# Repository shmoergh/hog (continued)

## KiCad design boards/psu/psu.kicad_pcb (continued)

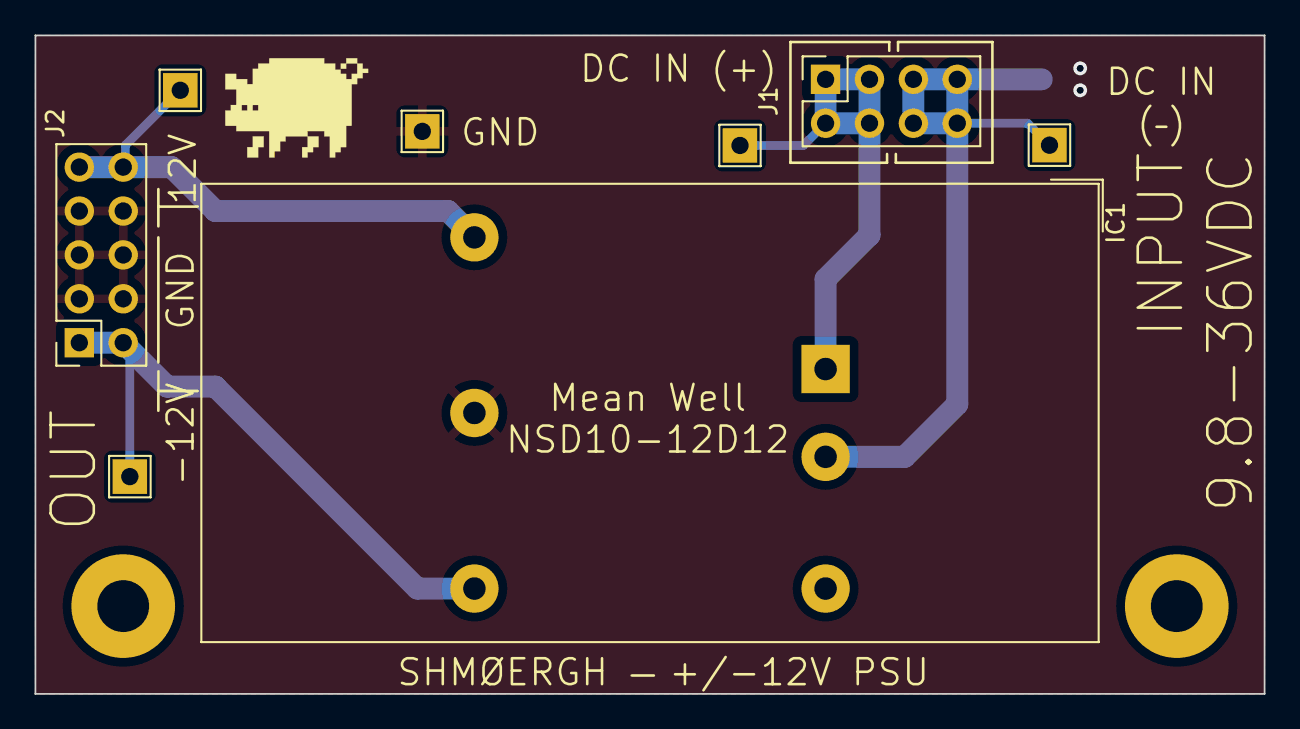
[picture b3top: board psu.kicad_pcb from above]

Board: 2 copper layers, 71.1 x 38.1 mm, 11 parts (1 on the bottom side), 5 nets.

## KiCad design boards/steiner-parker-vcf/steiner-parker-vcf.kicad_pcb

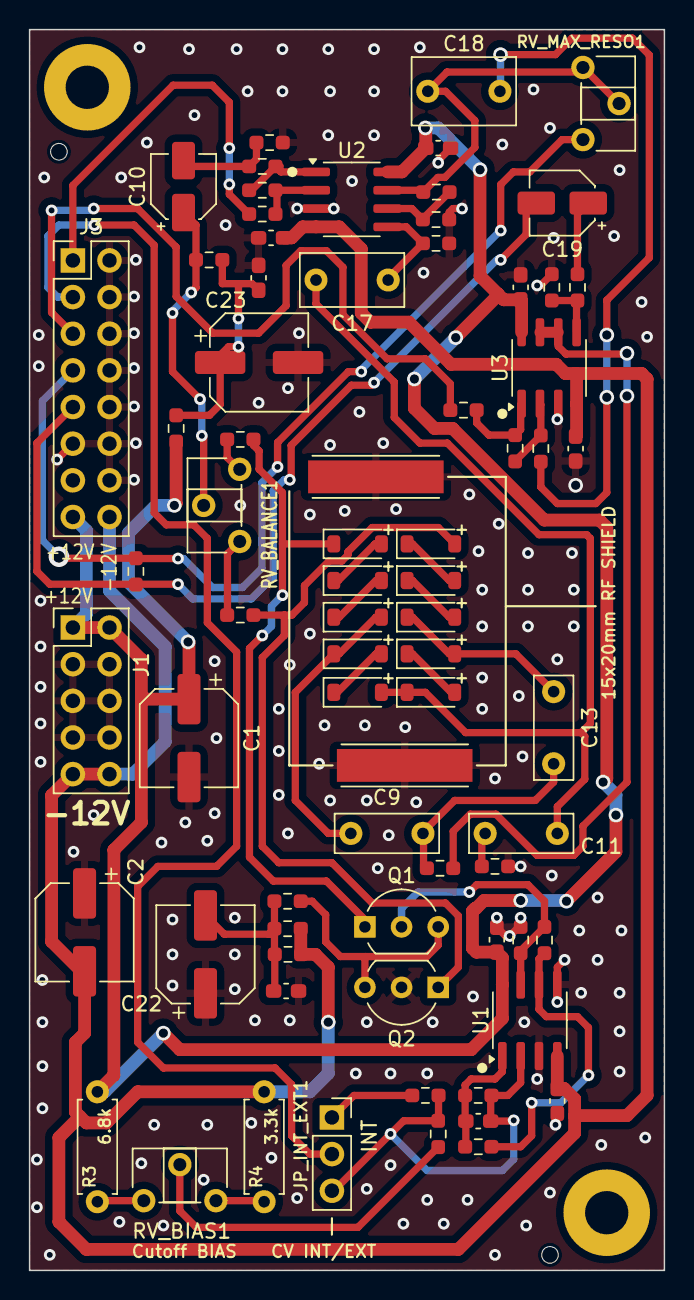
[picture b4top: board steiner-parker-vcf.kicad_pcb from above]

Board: 2 copper layers, 44.0 x 86.0 mm, 75 parts (0 on the bottom side), 47 nets.

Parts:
C1, C2, C22, C23: 100u; CP_Elec_6.3x7.7
C3, C4, C6, C7, C14, C16, C20, C21: 100n; C_0603_1608Metric_Pad1.08x0.95mm_HandSolder
C8: 10n; C_0603_1608Metric_Pad1.08x0.95mm_HandSolder
C9, C11, C13: 1n (Foil); C_Rect_L7.0mm_W2.5mm_P5.00mm
C10: 2.2u; CP_Elec_4x5.4
C17: 470n (foil); C_Rect_L7.0mm_W3.5mm_P5.00mm
C18: 1u (Foil); C_Rect_L7.0mm_W4.5mm_P5.00mm
C19: 10u; CP_Elec_4x5.4
D1, D2, D3, D4, D5, D6, D7, D8, D9, D10: 1N4148; D_SOD-123
H1, H2: MountingHole; MountingHole_3mm_Pad
J1: Eurorack Power; PinHeader_2x05_P2.54mm_Vertical
J2, J4: S1711-46R; HARWIN_S1711-46R
J3: Conn_02x08_Odd_Even; PinHeader_2x08_P2.54mm_Vertical
JP_INT_EXT1: Internal/External CV; PinSocket_1x03_P2.54mm_Vertical
Q1, Q2: BC547B; TO-92_Inline_Wide
R3: 6.8k; R_Axial_DIN0207_L6.3mm_D2.5mm_P7.62mm_Horizontal
R4: 3.3k; R_Axial_DIN0207_L6.3mm_D2.5mm_P7.62mm_Horizontal
R5, R11, R32: 10k; R_0603_1608Metric_Pad0.98x0.95mm_HandSolder
R6, R33, R34: 100k; R_0603_1608Metric_Pad0.98x0.95mm_HandSolder
R9, R31: 220k; R_0603_1608Metric_Pad0.98x0.95mm_HandSolder
R10: 56k; R_0603_1608Metric_Pad0.98x0.95mm_HandSolder
R12, R28: 47k; R_0603_1608Metric_Pad0.98x0.95mm_HandSolder
R13: 200k; R_0603_1608Metric_Pad0.98x0.95mm_HandSolder
R14: 180k; R_0603_1608Metric_Pad0.98x0.95mm_HandSolder
R15: 2.7k; R_0603_1608Metric_Pad0.98x0.95mm_HandSolder
R16, R24: 1.5k (1%); R_0603_1608Metric_Pad0.98x0.95mm_HandSolder
R17: 2.2k; R_0603_1608Metric_Pad0.98x0.95mm_HandSolder
R18: 100; R_0603_1608Metric_Pad0.98x0.95mm_HandSolder
R19: 390; R_0603_1608Metric_Pad0.98x0.95mm_HandSolder
R20, R21, R25, R35: 1k; R_0603_1608Metric_Pad0.98x0.95mm_HandSolder
R22: 3.9k; R_0603_1608Metric_Pad0.98x0.95mm_HandSolder
R23: 200; R_0603_1608Metric_Pad0.98x0.95mm_HandSolder
R26, R29: 1M; R_0603_1608Metric_Pad0.98x0.95mm_HandSolder
R27: 22k; R_0603_1608Metric_Pad0.98x0.95mm_HandSolder
RV_BALANCE1: 1k; Potentiometer_ACP_CA6-H2,5_Horizontal
RV_BIAS1: 10k; Potentiometer_ACP_CA6-H2,5_Horizontal
RV_MAX_RESO1: 100k; Potentiometer_ACP_CA6-H2,5_Horizontal
U1, U2, U3: TL072; SOIC-8_3.9x4.9mm_P1.27mm

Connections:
+12V: C1.1, C3.1, C6.1, C20.1, J1.1, J1.2, J3.15, R3.2, R19.1, U1.8 (V+), U2.8 (V+), U3.8 (V+)
-12V: C2.2, C4.2, C7.2, C21.2, J1.9, J1.10, J3.16, R4.2, R18.2, R23.2, U1.4 (V-), U2.4 (V-), U3.4 (V-)
AUDIO_IN: J3.1, R5.2
AUDIO_OUT: J3.5, R35.1
CUTOFF: J3.3, JP_INT_EXT1.2 (C)
GND: C1.2, C2.1, C3.2, C4.1, C6.2, C7.1, C14.2, C16.2, C20.2, C21.1, C22.1, C23.2, J1.3, J1.4, J1.5, J1.6, J1.7, J1.8, J2.1 (SHIELD), J3.2, J3.4, J3.6, J3.8, J3.10, J3.11, J3.12, J3.14, J4.1 (SHIELD), Q2.2 (B), R14.2, R17.2, R21.2, R26.2, R27.2, R29.2, U1.3 (+), U1.5 (+), U2.3 (+), U3.3 (+)
unnamed: C8.1, R10.1, R13.2, U1.1
unnamed: C10.1, R20.2, RV_BALANCE1.2
unnamed: C10.2, R12.1, R14.1
unnamed: C11.2, R21.1
unnamed: C9.2, C13.2, R25.2
unnamed: C14.1, C22.2, R18.1, R22.2, R23.1
unnamed: C16.1, C23.1, R19.2, R20.1
unnamed: C18.1, R32.2
unnamed: C18.2, R28.1, RV_MAX_RESO1.1, RV_MAX_RESO1.2, U2.7
unnamed: C19.1, R31.1
unnamed: D1.2 (A), D2.1 (K)
unnamed: D1.1 (K), Q1.1 (C), R16.2
unnamed: D2.2 (A), D3.1 (K)
unnamed: C9.1, D3.2 (A), D4.1 (K)
unnamed: D4.2 (A), D5.1 (K)
unnamed: C11.1, C17.2, D5.2 (A), D6.1 (K)
unnamed: D6.2 (A), D7.1 (K)
unnamed: C13.1, D7.2 (A), D8.1 (K)
unnamed: D8.2 (A), D9.1 (K)
unnamed: D10.2 (A), Q2.1 (C), R24.2
unnamed: D9.2 (A), D10.1 (K)
unnamed: JP_INT_EXT1.1 (A), R6.2
unnamed: C8.2, JP_INT_EXT1.3 (B), R6.1, R9.1, R10.2, U1.2 (-)
unnamed: Q1.2 (B), R15.1, R17.1, U1.7
unnamed: Q1.3 (E), Q2.3 (E), R22.1
unnamed: R3.1, RV_BIAS1.1
unnamed: R4.1, RV_BIAS1.3
unnamed: R9.2, RV_BIAS1.2
unnamed: R11.1, R12.2, U2.1
unnamed: R16.1, RV_BALANCE1.3
unnamed: R24.1, RV_BALANCE1.1
unnamed: R34.1, R35.2, U3.1
unnamed: R13.1, R15.2, U1.6 (-)
unnamed: R5.1, R11.2, U2.2 (-)
unnamed: C17.1, R26.1, U2.5 (+)
unnamed: R27.1, R28.2, U2.6 (-)
unnamed: R32.1, R34.2, U3.2 (-)
unnamed: R29.1, R31.2, U3.5 (+)
unnamed: R25.1, U3.6 (-), U3.7
RESO_2: C19.2, J3.9, R33.2
RESO_3: J3.7, R33.1, RV_MAX_RESO1.3

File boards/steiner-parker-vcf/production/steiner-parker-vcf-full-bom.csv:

"Reference","Value","Datasheet","Footprint","Qty","DNP","LCSC","Part No.","Part URL","Vendor"
"C1,C2,C22,C23","100u","~","Capacitor_SMD:CP_Elec_6.3x7.7","4","","C2836437","","","JLCPCB"
"C3,C4,C6,C7,C14,C16,C20,C21","100n","~","Capacitor_SMD:C_0603_1608Metric_Pad1.08x0.95mm_HandSolder","8","","C14663","","","JLCPCB"
"C8","10n","~","Capacitor_SMD:C_0603_1608Metric_Pad1.08x0.95mm_HandSolder","1","","C57112","","","JLCPCB"
"C9,C11,C13","1n (Foil)","~","Capacitor_THT:C_Rect_L7.0mm_W2.5mm_P5.00mm","3","","","80-R82EC1100SH50J ","https://mou.sr/3ZRLX4F","Mouser"
"C10","2.2u","~","Capacitor_SMD:CP_Elec_4x5.4","1","","C43242","","","JLCPCB"
"C17","470n (foil)","~","Capacitor_THT:C_Rect_L7.0mm_W3.5mm_P5.00mm","1","","","80-R82EC1470DQ50K ","https://mou.sr/4g5F5Xb","Mouser"
"C18","1u (Foil)","~","Capacitor_THT:C_Rect_L7.0mm_W4.5mm_P5.00mm","1","","","80-R82EC4100Z370K ","https://mou.sr/3ZROEn2","Mouser"
"C19","10u","~","Capacitor_SMD:CP_Elec_4x5.4","1","","C72485","","","JLCPCB"
"D1,D2,D3,D4,D5,D6,D7,D8,D9,D10","1N4148","~","Diode_SMD:D_SOD-123","10","","C81598","","","JLCPCB"
"J1","Eurorack Power","~","Connector_PinHeader_2.54mm:PinHeader_2x05_P2.54mm_Vertical","1","","","737-RS2-10-G ","https://mou.sr/3ZTZokP","Mouser"
"J3","Conn_02x08_Odd_Even","~","Connector_PinHeader_2.54mm:PinHeader_2x08_P2.54mm_Vertical","1","","","737-RS2-16-G ","https://mou.sr/3DcrsXN","Mouser"
"JP_INT_EXT1","Internal/External CV","~","Connector_PinSocket_2.54mm:PinSocket_1x03_P2.54mm_Vertical","1","","","737-PH1-20-UA ","https://mou.sr/4gqTRHQ","Mouser"
"Q1","BC547B","https://www.onsemi.com/pub/Collateral/BC550-D.pdf","Package_TO_SOT_THT:TO-92_Inline_Wide","1","","","637-BC547B ","https://mou.sr/49DWqUL","Mouser"
"R3","6.8k","~","Shmoergh_Custom_Footprints:R_Axial_DIN0207_L6.3mm_D2.5mm_P7.62mm_Horizontal","1","","","303-MF0W4FF6801B00 ","https://mou.sr/4gAS3Mw","Mouser"
"R4","3.3k","~","Shmoergh_Custom_Footprints:R_Axial_DIN0207_L6.3mm_D2.5mm_P7.62mm_Horizontal","1","","","303-CFR0W4J0332B00 ","https://mou.sr/41AgNQH","Mouser"
"R5,R11,R32","10k","~","Resistor_SMD:R_0603_1608Metric_Pad0.98x0.95mm_HandSolder","3","","C25804","","","JLCPCB"
"R6,R33,R34","100k","~","Resistor_SMD:R_0603_1608Metric_Pad0.98x0.95mm_HandSolder","3","","C25803","","","JLCPCB"
"R9,R31","220k","~","Resistor_SMD:R_0603_1608Metric_Pad0.98x0.95mm_HandSolder","2","","C22961","","","JLCPCB"
"R10","56k","~","Resistor_SMD:R_0603_1608Metric_Pad0.98x0.95mm_HandSolder","1","","C23206","","","JLCPCB"
"R12,R28","47k","~","Resistor_SMD:R_0603_1608Metric_Pad0.98x0.95mm_HandSolder","2","","C25819","","","JLCPCB"
"R13","200k","~","Resistor_SMD:R_0603_1608Metric_Pad0.98x0.95mm_HandSolder","1","","C25811","","","JLCPCB"
"R14","180k","~","Resistor_SMD:R_0603_1608Metric_Pad0.98x0.95mm_HandSolder","1","","C3016400","","","JLCPCB"
"R15","2.7k","~","Resistor_SMD:R_0603_1608Metric_Pad0.98x0.95mm_HandSolder","1","","C13167","","","JLCPCB"
"R16,R24","1.5k (1%)","~","Resistor_SMD:R_0603_1608Metric_Pad0.98x0.95mm_HandSolder","2","","C22843","","","JLCPCB"
"R17","2.2k","~","Resistor_SMD:R_0603_1608Metric_Pad0.98x0.95mm_HandSolder","1","","C4190","","","JLCPCB"
"R18","100","~","Resistor_SMD:R_0603_1608Metric_Pad0.98x0.95mm_HandSolder","1","","C22775","","","JLCPCB"
"R19","390","~","Resistor_SMD:R_0603_1608Metric_Pad0.98x0.95mm_HandSolder","1","","C23151","","","JLCPCB"
"R20,R21,R25,R35","1k","~","Resistor_SMD:R_0603_1608Metric_Pad0.98x0.95mm_HandSolder","4","","C21190","","","JLCPCB"
"R22","3.9k","~","Resistor_SMD:R_0603_1608Metric_Pad0.98x0.95mm_HandSolder","1","","C23018","","","JLCPCB"
"R23","200","~","Resistor_SMD:R_0603_1608Metric_Pad0.98x0.95mm_HandSolder","1","","C8218","","","JLCPCB"
"R26,R29","1M","~","Resistor_SMD:R_0603_1608Metric_Pad0.98x0.95mm_HandSolder","2","","C22935","","","JLCPCB"
"R27","22k","~","Resistor_SMD:R_0603_1608Metric_Pad0.98x0.95mm_HandSolder","1","","C31850","","","JLCPCB"
"RV_BALANCE1","1k","~","Potentiometer_THT:Potentiometer_ACP_CA6-H2,5_Horizontal","1","","","531-PT6KH-1K ","https://mou.sr/3DgNY1x","Mouser"
"RV_BIAS1","10k","~","Potentiometer_THT:Potentiometer_ACP_CA6-H2,5_Horizontal","1","","","531-PT6KH-10K ","https://mou.sr/49CavSt","Mouser"
"RV_MAX_RESO1","100k","~","Potentiometer_THT:Potentiometer_ACP_CA6-H2,5_Horizontal","1","","","531-PT6KH104A1010PM ","https://mou.sr/3OVlmh2","Mouser"
"U1,U2,U3","TL072","http://www.ti.com/lit/ds/symlink/tl071.pdf","Package_SO:SOIC-8_3.9x4.9mm_P1.27mm","3","","C6961","","","JLCPCB"

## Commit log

2024-10-29 Rev 3
2024-11-02 Added firmware to MIDI2CV
2024-11-10 Folder restructure
2024-11-10 Added schematics docs
2024-11-23 Added LFO LED resistor values
    https://github.com/shmoergh/hog/issues/24
2024-11-23 Updated MIDI IO
    https://github.com/shmoergh/hog/issues/24
    UI: Set default pin of PITCH and GATE inputs to MIDI converter's respective outputs
    UI: Add 12V power for MIDI2CV converter connector
2024-11-23 Updated RESO pot resistance value
    ref. https://github.com/shmoergh/hog/issues/24
    UI: Update dirty dual pot to 50kΩ (100kΩ is not available at Mouser)
2024-11-23 Updated minimum Cutoff resistance on filter
    https://github.com/shmoergh/hog/issues/24
    Filter: update R4 value to 3.3kΩ. This allows better minimum cutoff value
2024-11-23 Removed VCA rejection trimpot
    https://github.com/shmoergh/hog/issues/8
    Also updated Core board footprints to work with fcking KiCad 8
2024-11-23 Replaced mixer feedback resistor to SMD
    https://github.com/shmoergh/hog/issues/9
2024-11-23 Replaced mixer input caps to SMD
    https://github.com/shmoergh/hog/issues/26
2024-11-23 Added THT footprint to J111 in VCOs
    https://github.com/shmoergh/hog/issues/10
2024-11-23 Separate Core board to versions
    https://github.com/shmoergh/hog/issues/7
    - Removed precision +/-5V circuit and its outputs as it's unnecessary for the Core board
2024-11-23 Cleanup
2024-11-24 Streamline 'Stable' Core board
    https://github.com/shmoergh/hog/issues/7
    - Remove 12V terminal input
    - Reposition Eurorack power connector to right so it makes space for tuning
    - Remove all unnecessary thermal compensation pseudo components
    - Reposition tuning trimmers
2024-11-30 Repositioned connectors on Core board
    ref https://github.com/shmoergh/hog/issues/30
    Connectors have to be aligned on the 1mm grid on the Core board so that it's easy to align the connector pairs on the UI board.
2024-11-30 Updated UI board connector positions
    https://github.com/shmoergh/hog/issues/31
    Moving the tuner trimmers on the Core board required to reposition the connector headers too. This also had to be done on the UI board otherwise it won't be possible to connect the two boards.
2024-11-30 Added FAB drawings of all boards for UI
    As a preparation for making everything more streamlined
2024-12-01 Replaced wired MIDI connection to pins
    https://github.com/shmoergh/hog/issues/32
    MIDI connection was done with manual wired NTS connectors. Now they are replaced with pins and pinheaders just like the other boards.
2024-12-08 Created PSU board
    https://github.com/shmoergh/hog/issues/4
2024-12-09 Created BOM for PSU board
    ref https://github.com/shmoergh/hog/issues/19
2024-12-09 Removed backpanel IO conn. + fixed drone voltage
    https://github.com/shmoergh/hog/issues/37
    The IO back panel connector on the UI board is a leftover from an earlier prototype. Can be removed.
    https://github.com/shmoergh/hog/issues/36
    ATM the gate voltage for drone mode is fixed to 5V which makes it quieter than the normal gate. Drone mode gate voltage should be 8V.
2024-12-13 Updated and checked Core board BOM
    ref https://github.com/shmoergh/hog/issues/19
2024-12-14 Added JLCPCB production files to Core
    ref https://github.com/shmoergh/hog/issues/19
2024-12-14 Added Core full BOM
    ref https://github.com/shmoergh/hog/issues/19
2024-12-14 Added Core Mouser BOM csv and Production readme
    ref https://github.com/shmoergh/hog/issues/19
2024-12-14 Added BOM and gerber for PSU board
    ref https://github.com/shmoergh/hog/issues/19
2024-12-14 Added production files for VCF
    ref https://github.com/shmoergh/hog/issues/19
2024-12-14 Added production files to MIDI2CV board
    ref https://github.com/shmoergh/hog/issues/19
2024-12-14 Added production files for the UI board
    ref https://github.com/shmoergh/hog/issues/19
2024-12-14 Fixed PSU and UI sizing bug
2024-12-15 Re-added UI board BOMs
2024-12-15 Reupload PDFs
2024-12-15 Restructured PDFs
2024-12-21 Added enclosure layout for top and back panels
    ref https://github.com/shmoergh/hog/issues/38
2025-01-12 Replaced VCA dual BJT footprint
2025-01-26 Added pico-lib
2025-03-16 Updated resistor Mouser no's and added full bom
    - Some of the THT resistors in the BOM were referencing to products with min. 1000 pcs order quantity
    - Added a full Mouser BOM which can be used to order all Mouser components by uploading to their BOM tool: https://hu.mouser.com/bom/
2025-05-15 Redesign midi2cv using SMD components
2026-04-16 Markdown cleanup
